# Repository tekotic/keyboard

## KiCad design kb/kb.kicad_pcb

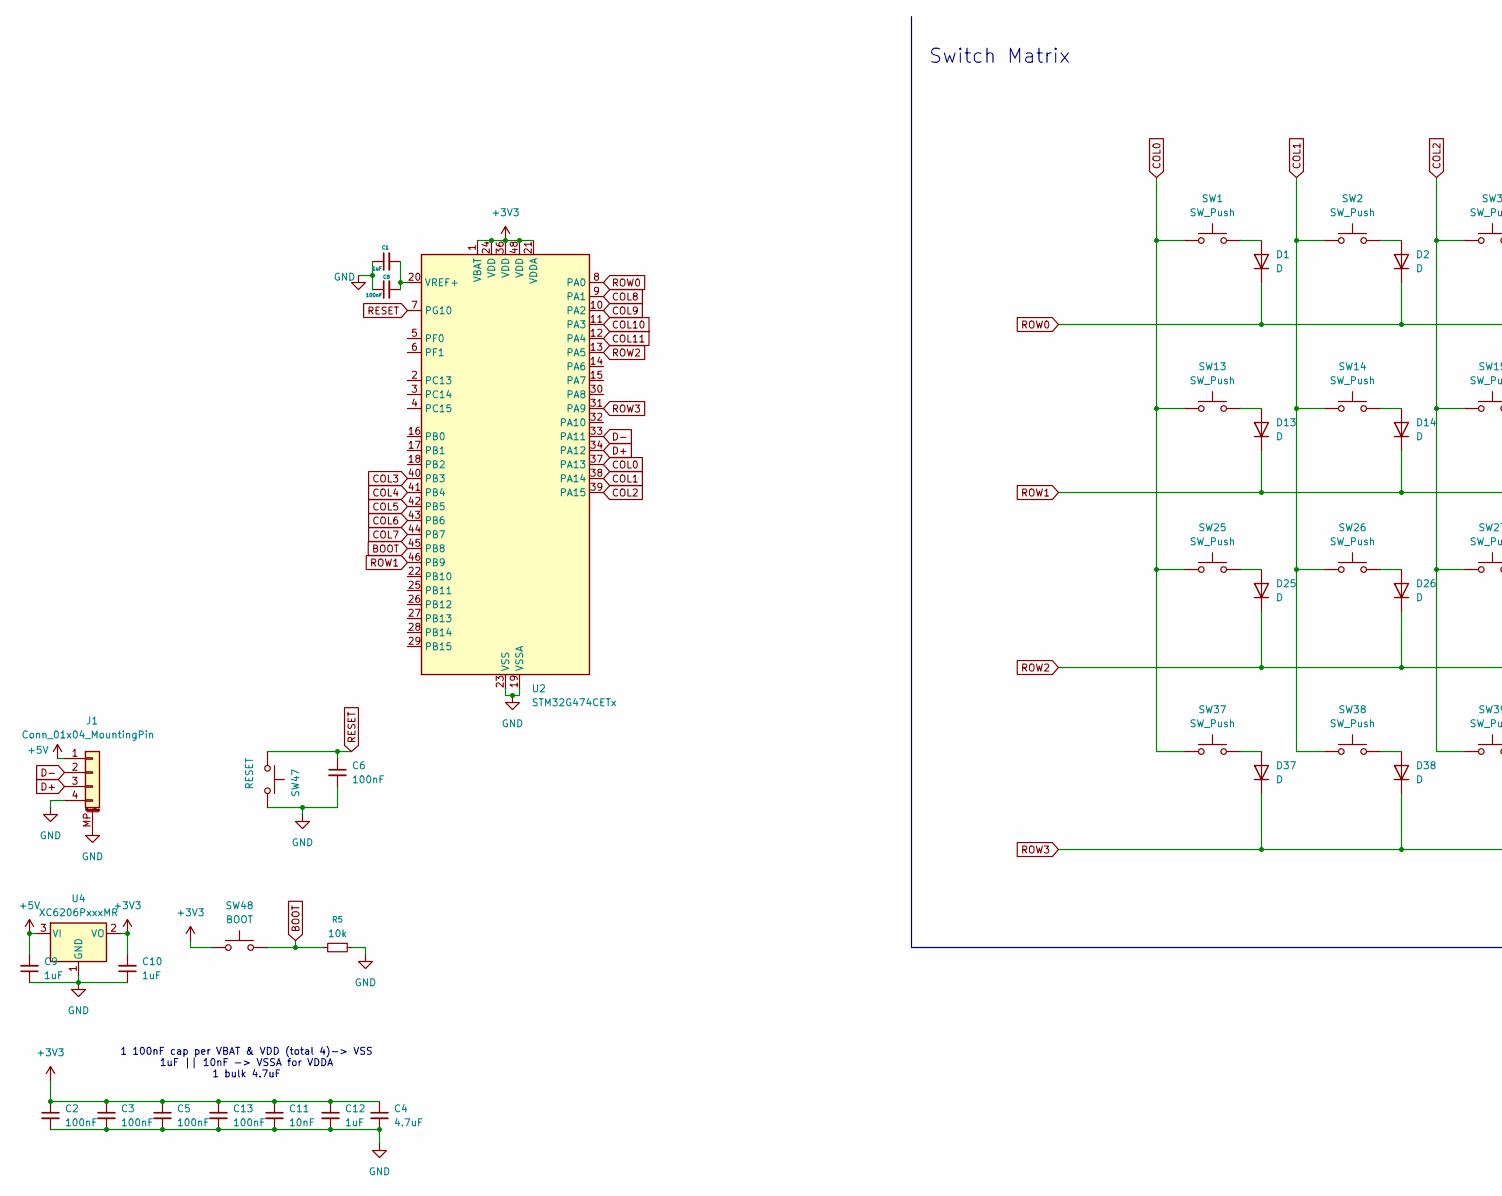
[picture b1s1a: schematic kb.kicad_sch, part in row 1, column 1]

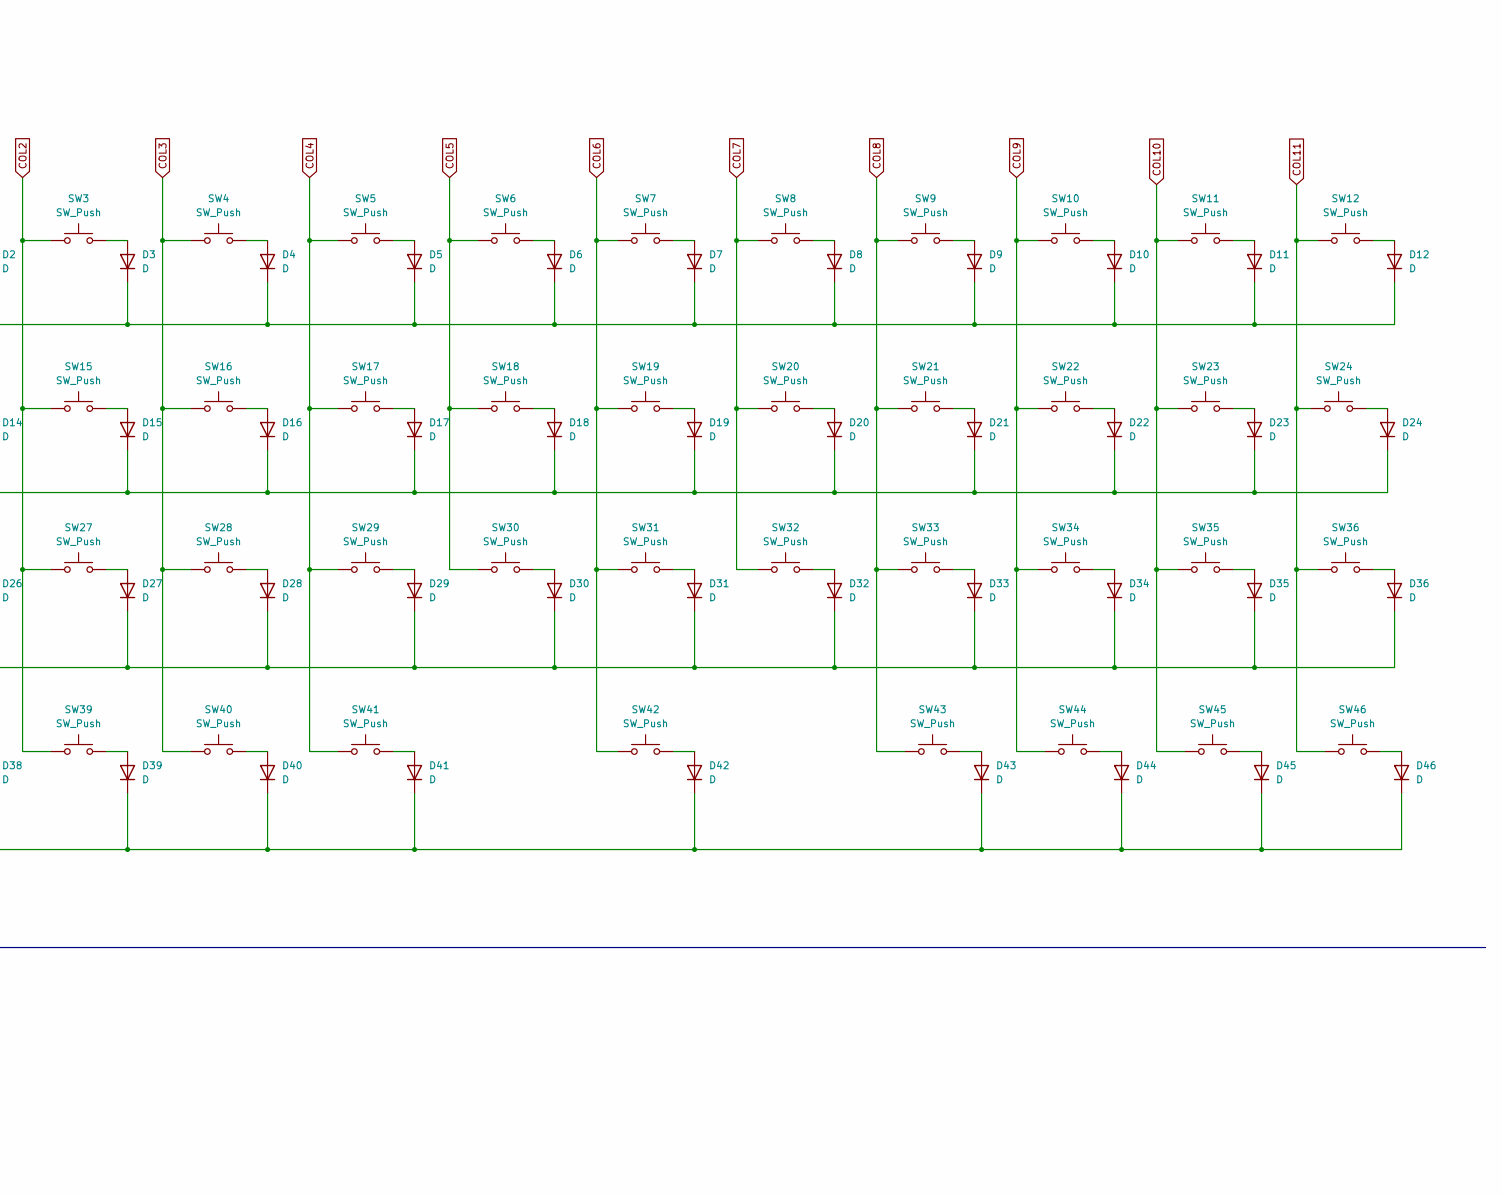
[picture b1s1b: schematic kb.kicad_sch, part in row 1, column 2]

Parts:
C1, C9, C10, C12: 1uF; C_0402_1005Metric
C2, C3, C5, C6, C8, C13: 100nF; C_0402_1005Metric
C4: 4.7uF; C_0402_1005Metric
C11: 10nF; C_0402_1005Metric
D1, D2, D3, D4, D5, D6, D7, D8, D9, D10, D11, D12, D13, D14, D15, D16, D17, D18, D19, D20, D21, D22, D23, D24, D25, D26, D27, D28, D29, D30, D31, D32, D33, D34, D35, D36, D37, D38, D39, D40, D41, D42, D43, D44, D45, D46: D; D_0805_2012Metric
J1: Conn_01x04_MountingPin; Molex_Pico-EZmate_78171-0004_1x04-1MP_P1.20mm_Vertical
R5: 10k; R_0402_1005Metric
SW1, SW24: SW_Push; MX-Solderable-1.5U
SW2, SW3, SW4, SW5, SW6, SW7, SW8, SW9, SW10, SW11, SW14, SW15, SW16, SW17, SW18, SW19, SW20, SW21, SW22, SW23, SW26, SW27, SW28, SW29, SW30, SW31, SW32, SW33, SW34, SW35, SW36, SW38, SW41, SW44, SW45, SW46: SW_Push; MX-Solderable-1U
SW12, SW13: SW_Push; MX-Solderable-1.75U
SW25, SW40, SW42: SW_Push; MX-Solderable-2.25U
SW37, SW39, SW43: SW_Push; MX-Solderable-1.25U
SW47: RESET; SW_SPST_SKQG_WithStem
SW48: BOOT; SW_SPST_SKQG_WithStem
U2: STM32G474CETx; LQFP-48_7x7mm_P0.5mm
U4: XC6206PxxxMR; SOT-23-3

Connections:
+3V3: C2.1, C3.1, C4.1, C5.1, C10.2, C11.1, C12.1, C13.1, SW48.1, U2.1 (VBAT), U2.21 (VDDA), U2.24 (VDD), U2.36 (VDD), U2.48 (VDD), U4.2 (VO)
+5V: C9.2, J1.1, U4.3 (VI)
BOOT: R5.1, SW48.2, U2.45 (PB8)
COL0: SW1.1, SW13.1, SW25.1, SW37.1, U2.37 (PA13)
COL1: SW2.1, SW14.1, SW26.1, SW38.1, U2.38 (PA14)
COL2: SW3.1, SW15.1, SW27.1, SW39.1, U2.39 (PA15)
COL3: SW4.1, SW16.1, SW28.1, SW40.1, U2.40 (PB3)
COL4: SW5.1, SW17.1, SW29.1, SW41.1, U2.41 (PB4)
COL5: SW6.1, SW18.1, SW30.1, U2.42 (PB5)
COL6: SW7.1, SW19.1, SW31.1, SW42.1, U2.43 (PB6)
COL7: SW8.1, SW20.1, SW32.1, U2.44 (PB7)
COL8: SW9.1, SW21.1, SW33.1, SW43.1, U2.9 (PA1)
COL9: SW10.1, SW22.1, SW34.1, SW44.1, U2.10 (PA2)
COL10: SW11.1, SW23.1, SW35.1, SW45.1, U2.11 (PA3)
COL11: SW12.1, SW24.1, SW36.1, SW46.1, U2.12 (PA4)
D+: J1.3, U2.34 (PA12)
D-: J1.2, U2.33 (PA11)
GND: C1.1, C2.2, C3.2, C4.2, C5.2, C6.2, C8.1, C9.1, C10.1, C11.2, C12.2, C13.2, J1.4, J1.MP (MountPin), R5.2, SW47.2, U2.19 (VSSA), U2.23 (VSS), U2.35 (VSS), U2.47 (VSS), U4.1 (GND)
unnamed: D1.2 (A), SW1.2
unnamed: D2.2 (A), SW2.2
unnamed: D3.2 (A), SW3.2
unnamed: D4.2 (A), SW4.2
unnamed: D5.2 (A), SW5.2
unnamed: D6.2 (A), SW6.2
unnamed: D7.2 (A), SW7.2
unnamed: D8.2 (A), SW8.2
unnamed: D9.2 (A), SW9.2
unnamed: D10.2 (A), SW10.2
unnamed: D11.2 (A), SW11.2
unnamed: D12.2 (A), SW12.2
unnamed: D13.2 (A), SW13.2
unnamed: D14.2 (A), SW14.2
unnamed: D15.2 (A), SW15.2
unnamed: D16.2 (A), SW16.2
unnamed: D17.2 (A), SW17.2
unnamed: D18.2 (A), SW18.2
unnamed: D19.2 (A), SW19.2
unnamed: D20.2 (A), SW20.2
unnamed: D21.2 (A), SW21.2
unnamed: D22.2 (A), SW22.2
unnamed: D23.2 (A), SW23.2
unnamed: D24.2 (A), SW24.2
unnamed: D25.2 (A), SW25.2
unnamed: D26.2 (A), SW26.2
unnamed: D27.2 (A), SW27.2
unnamed: D28.2 (A), SW28.2
unnamed: D29.2 (A), SW29.2
unnamed: D30.2 (A), SW30.2
unnamed: D31.2 (A), SW31.2
unnamed: D32.2 (A), SW32.2
unnamed: D33.2 (A), SW33.2
unnamed: D34.2 (A), SW34.2
unnamed: D35.2 (A), SW35.2
unnamed: D36.2 (A), SW36.2
unnamed: D37.2 (A), SW37.2
unnamed: D38.2 (A), SW38.2
unnamed: D39.2 (A), SW39.2
unnamed: D40.2 (A), SW40.2
unnamed: D41.2 (A), SW41.2
unnamed: D42.2 (A), SW42.2
unnamed: D43.2 (A), SW43.2
unnamed: D44.2 (A), SW44.2
unnamed: D45.2 (A), SW45.2
unnamed: D46.2 (A), SW46.2
unnamed: C1.2, C8.2, U2.20 (VREF+)
RESET: C6.1, SW47.1, U2.7 (PG10)
ROW0: D1.1 (K), D2.1 (K), D3.1 (K), D4.1 (K), D5.1 (K), D6.1 (K), D7.1 (K), D8.1 (K), D9.1 (K), D10.1 (K), D11.1 (K), D12.1 (K), U2.8 (PA0)
ROW1: D13.1 (K), D14.1 (K), D15.1 (K), D16.1 (K), D17.1 (K), D18.1 (K), D19.1 (K), D20.1 (K), D21.1 (K), D22.1 (K), D23.1 (K), D24.1 (K), U2.46 (PB9)
ROW2: D25.1 (K), D26.1 (K), D27.1 (K), D28.1 (K), D29.1 (K), D30.1 (K), D31.1 (K), D32.1 (K), D33.1 (K), D34.1 (K), D35.1 (K), D36.1 (K), U2.13 (PA5)
ROW3: D37.1 (K), D38.1 (K), D39.1 (K), D40.1 (K), D41.1 (K), D42.1 (K), D43.1 (K), D44.1 (K), D45.1 (K), D46.1 (K), U2.31 (PA9)

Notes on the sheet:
1 100nF cap per VBAT & VDD (total 4)-> VSS 1uF || 10nF -> VSSA for VDDA 1 bulk 4.7uF
Switch Matrix

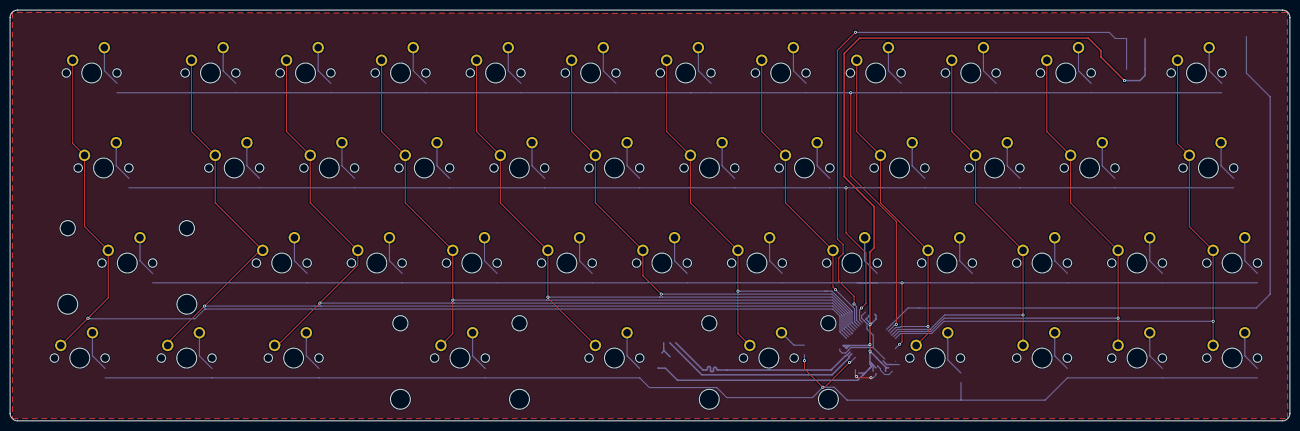
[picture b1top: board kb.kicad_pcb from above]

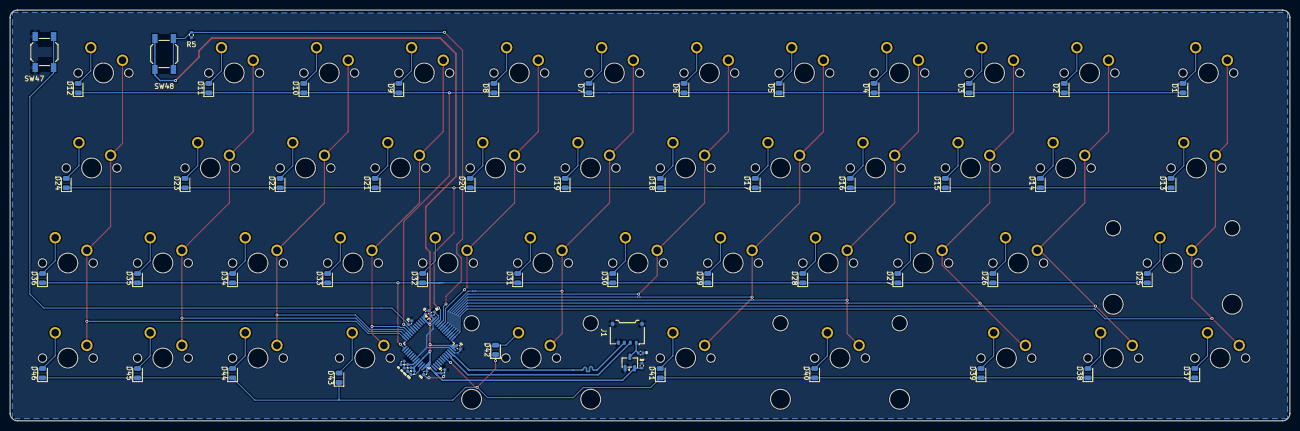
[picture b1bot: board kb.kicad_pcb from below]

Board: 2 copper layers, 256.5 x 82.3 mm, 110 parts (64 on the bottom side), 70 nets.

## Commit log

2025-10-28 Initalized
    Project and files created
2025-10-28 Added submodules
2025-10-28 Added symbol and footprint libraries, 3D path variable
2025-10-31 Made Schematic, PCB Base
    Created schematic with matrix grid, added footprints.
    imported to pcb, placed diodes
2025-10-31 Updated Schematic
    Updated Schematic
2025-10-31 Improved routing
    Edited schematic column layout,
    Manually routed necessary keys on pcb
2025-11-01 1.5u enter, fixed schematic
    Fixed schematic & pcb for 1.5u enter layout
2025-11-08 STM32 + Unified Daughterboard Implementation
    Switched to run off STM32 and S1.1 Unified Daughterboard.
    Wired rows and cols
2025-11-09 Wired PCB
    Finished wiring PCB
2025-12-15 Fixed Board Side
    Fixed Side of board
2025-12-16 Fixed Decoupling
    Fix decoupling cap placement + amounts, added ground layer, thickened vdd traces, completed routing
2025-12-17 Improved Ground Net
    Rewired some components, fixed ground layer, seperated VSSA from VSS
2025-12-18 Fixed usb IO pins
    Moved USB IO pins to 33/34 (PA11/PA12) where they belong
2025-12-18 Removed ESD component
    Due to built-in ESD functionality on daughterboard, onboard ESD protection is unnecessary
2025-12-18 Moved LDO and MOLEX port
    Moved LDO and MOLEX port to minimize wire length after removing ESD protector. Also improved wiring and moved some capacitors
2025-12-19 Added NSRT, Fixed Pins
    Fixed boot pin and reset pin assignments, rerouted accordingly
2025-12-19 Shrunk passive footprints
    Switched footprint of passives from 0805 to 0402 and rewired accordingly
2025-12-20 Moved LDO
    Moved LDO away from MCU for thermals, ensured all fills are grounded
2025-12-20 Moved LDO
    Moved LDO away from MCU for thermals, ensured all fills are grounded
2025-12-23 Changed layout
    Changed layout for more common footprint sizes, moved USB components for more stab clearance, added layout file to src
2025-12-23 Layout Fix
2025-12-23 Added edge cuts
    Added edge cuts (dimensioned 82.325 x 256.525 mm, 1.5mm diameter fillet)
2025-12-23 Net improvement to edge cut
